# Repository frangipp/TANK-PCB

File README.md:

Dans le cadre d’un projet étudiant en binôme à l’ESEO Angers.

Développement d’un "TANK" : un petit robot à entraînement différentiel. Il sera commandé par Bluetooth via une application Android.
Pour l’utilisateur, l’objectif sera d’entrer en collision avec le TANK adverse. Chaque collision rapporte des points.

Détails techniques :

* Microcontrôleur STM32G431
* Module Bluetooth HC-05
* Négociation USB Power Delivery (STUSB4531)
* Chargeur et BMS pour batterie Li-ion (power management : BQ24800, équilibrage des cellules : BQ76905)
* Driver moteur LMD18200. Moteurs jusqu’à 55 V (théorique) et 3 A. On utilise ici des Maxon en 12 V.

À titre personnel, ce projet me permet surtout de tester la norme USB Power Delivery ainsi que la charge d’une batterie.

### Restrictions on Automated Processing and AI Usage

The author explicitly prohibits any text and data mining (TDM), scraping, indexing, or use of this project for training, evaluating, or operating artificial intelligence systems, unless prior written permission is obtained.

All rights are reserved in this regard, including under applicable EU directives on text and data mining.

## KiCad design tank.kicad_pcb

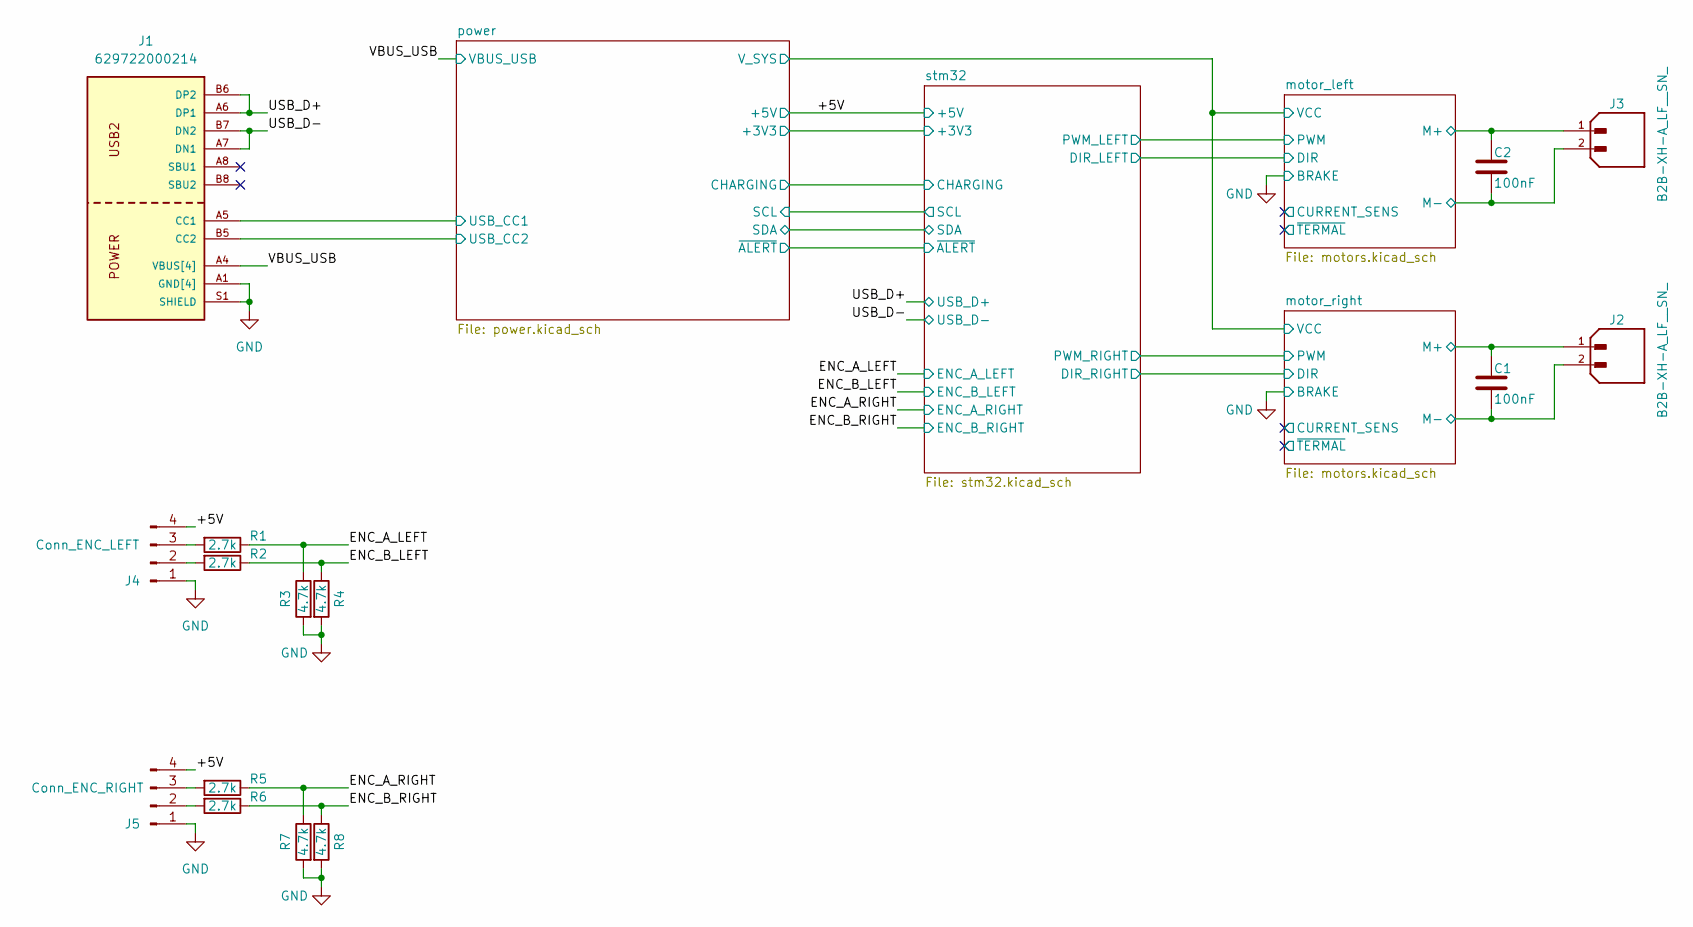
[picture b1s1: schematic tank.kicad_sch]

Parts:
C1, C2: 100nF; C_0603_1608Metric
J1: 629722000214
J2, J3: B2B-XH-A_LF__SN_; JST_B2B-XH-A_LF__SN_
J4: Conn_ENC_LEFT; PinHeader_1x04_P2.54mm_Vertical
J5: Conn_ENC_RIGHT; PinHeader_1x04_P2.54mm_Vertical
R1, R2, R5, R6: 2.7k; R_0603_1608Metric
R3, R4, R7, R8: 4.7k; R_0603_1608Metric

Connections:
/+5V: J4.4, J5.4; also elsewhere on the board
/ENC_A_LEFT: R1.1, R3.1; also elsewhere on the board
/ENC_A_RIGHT: R5.1, R7.1; also elsewhere on the board
/ENC_B_LEFT: R2.1, R4.1; also elsewhere on the board
/ENC_B_RIGHT: R6.1, R8.1; also elsewhere on the board
/USB_D+: J1.A6 (DP1), J1.B6 (DP2); also elsewhere on the board
/USB_D-: J1.A7 (DN1), J1.B7 (DN2); also elsewhere on the board
/VBUS_USB: J1.A4 (VBUS[4]), J1.A9 (VBUS[4]), J1.B4 (VBUS[4]), J1.B9 (VBUS[4]); also elsewhere on the board
/motor_left/M+: C2.1, J3.1; also elsewhere on the board
/motor_left/M-: C2.2, J3.2; also elsewhere on the board
/motor_right/M+: C1.1, J2.1; also elsewhere on the board
/motor_right/M-: C1.2, J2.2; also elsewhere on the board
/power/USB_CC1: J1.A5 (CC1); also elsewhere on the board
/power/USB_CC2: J1.B5 (CC2); also elsewhere on the board
GND: J1.A1 (GND[4]), J1.A12 (GND[4]), J1.B1 (GND[4]), J1.B12 (GND[4]), J1.S1 (SHIELD), J1.S2, J1.S3, J1.S4, J4.1, J5.1, R3.2, R4.2, R7.2, R8.2; also elsewhere on the board
unnamed: J4.2, R2.2
unnamed: J4.3, R1.2
unnamed: J5.2, R6.2
unnamed: J5.3, R5.2

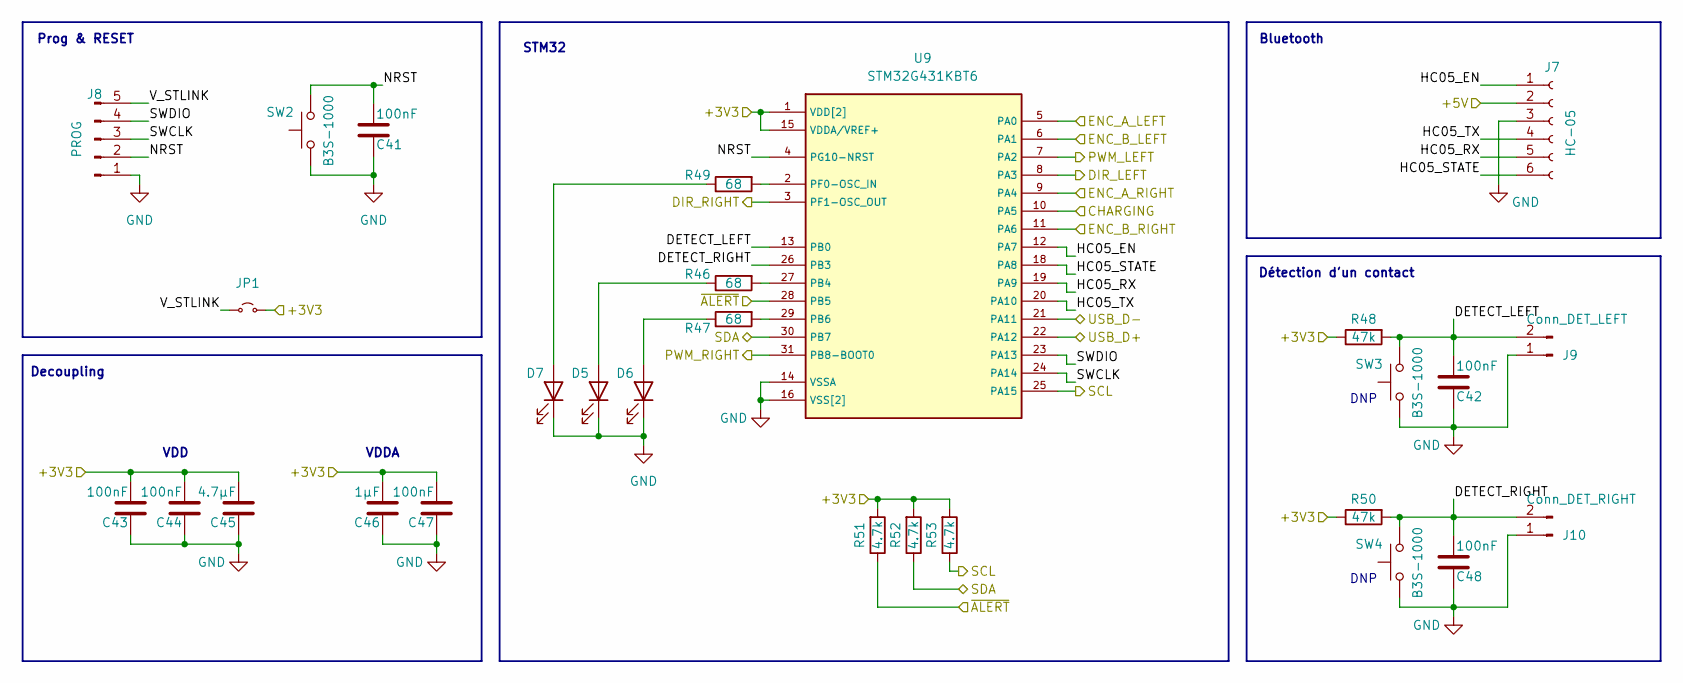
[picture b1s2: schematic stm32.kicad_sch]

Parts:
C41, C42, C43, C44, C47, C48: 100nF; C_0603_1608Metric
C45: 4.7µF; C_0805_2012Metric
C46: 1µF; C_0603_1608Metric
D5, D6, D7: LED; LED_0603_1608Metric
J7: HC-05; PinSocket_1x06_P2.54mm_Vertical
J8: PROG; PinHeader_1x05_P2.54mm_Vertical
J9: Conn_DET_LEFT; PinHeader_1x02_P2.54mm_Vertical
J10: Conn_DET_RIGHT; PinHeader_1x02_P2.54mm_Vertical
JP1: Jumper_2_Small_Open; PinHeader_1x02_P2.54mm_Vertical
R46, R47, R49: 68; R_0603_1608Metric
R48, R50: 47k; R_0603_1608Metric
R51, R52, R53: 4.7k; R_0603_1608Metric
SW2, SW3, SW4: B3S-1000; SW_SPST_B3S-1000
U9: STM32G431KBT6; QFP80P900X900X160-32N

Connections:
/+5V: J7.2; also elsewhere on the board
/ENC_A_LEFT: U9.5 (PA0); also elsewhere on the board
/ENC_A_RIGHT: U9.9 (PA4); also elsewhere on the board
/ENC_B_LEFT: U9.6 (PA1); also elsewhere on the board
/ENC_B_RIGHT: U9.11 (PA6); also elsewhere on the board
/USB_D+: U9.22 (PA12); also elsewhere on the board
/USB_D-: U9.21 (PA11); also elsewhere on the board
/motor_left/DIR: U9.8 (PA3); also elsewhere on the board
/motor_left/PWM: U9.7 (PA2); also elsewhere on the board
/motor_right/DIR: U9.3 (PF1-OSC_OUT); also elsewhere on the board
/motor_right/PWM: U9.31 (PB8-BOOT0); also elsewhere on the board
/power/CHARGING: U9.10 (PA5); also elsewhere on the board
/power/SCL: R53.1, U9.25 (PA15); also elsewhere on the board
/power/SDA: R52.1, U9.30 (PB7); also elsewhere on the board
/power/~ALERT: R51.1, U9.28 (PB5); also elsewhere on the board
/stm32/DETECT_LEFT: C42.2, J9.2, R48.2, SW3.2, U9.13 (PB0)
/stm32/DETECT_RIGHT: C48.2, J10.2, R50.2, SW4.2, U9.26 (PB3)
/stm32/HC05_EN: J7.1, U9.12 (PA7)
/stm32/HC05_RX: J7.5, U9.19 (PA9)
/stm32/HC05_STATE: J7.6, U9.18 (PA8)
/stm32/HC05_TX: J7.4, U9.20 (PA10)
/stm32/NRST: C41.2, J8.2, SW2.2, U9.4 (PG10-NRST)
/stm32/SWCLK: J8.3, U9.24 (PA14)
/stm32/SWDIO: J8.4, U9.23 (PA13)
/stm32/V_STLINK: J8.5, JP1.1 (A)
GND: C41.1, C42.1, C43.1, C44.1, C45.1, C46.1, C47.1, C48.1, D5.1 (K), D6.1 (K), D7.1 (K), J7.3, J8.1, J9.1, J10.1, SW2.1, SW3.1, SW4.1, U9.14 (VSSA), U9.16 (VSS[2]), U9.32 (VSS); also elsewhere on the board
unnamed: D5.2 (A), R46.1
unnamed: D6.2 (A), R47.1
unnamed: D7.2 (A), R49.1
unnamed: R46.2, U9.27 (PB4)
unnamed: R47.2, U9.29 (PB6)
unnamed: R49.2, U9.2 (PF0-OSC_IN)
VDD: C43.2, C44.2, C45.2, C46.2, C47.2, JP1.2 (B), R48.1, R50.1, R51.2, R52.2, R53.2, U9.1 (VDD[2]), U9.15 (VDDA/VREF+), U9.17 (VDD); also elsewhere on the board

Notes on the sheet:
VDDA
Détection d'un contact
Bluetooth
DNP
VDD
Decoupling
Prog & RESET
STM32

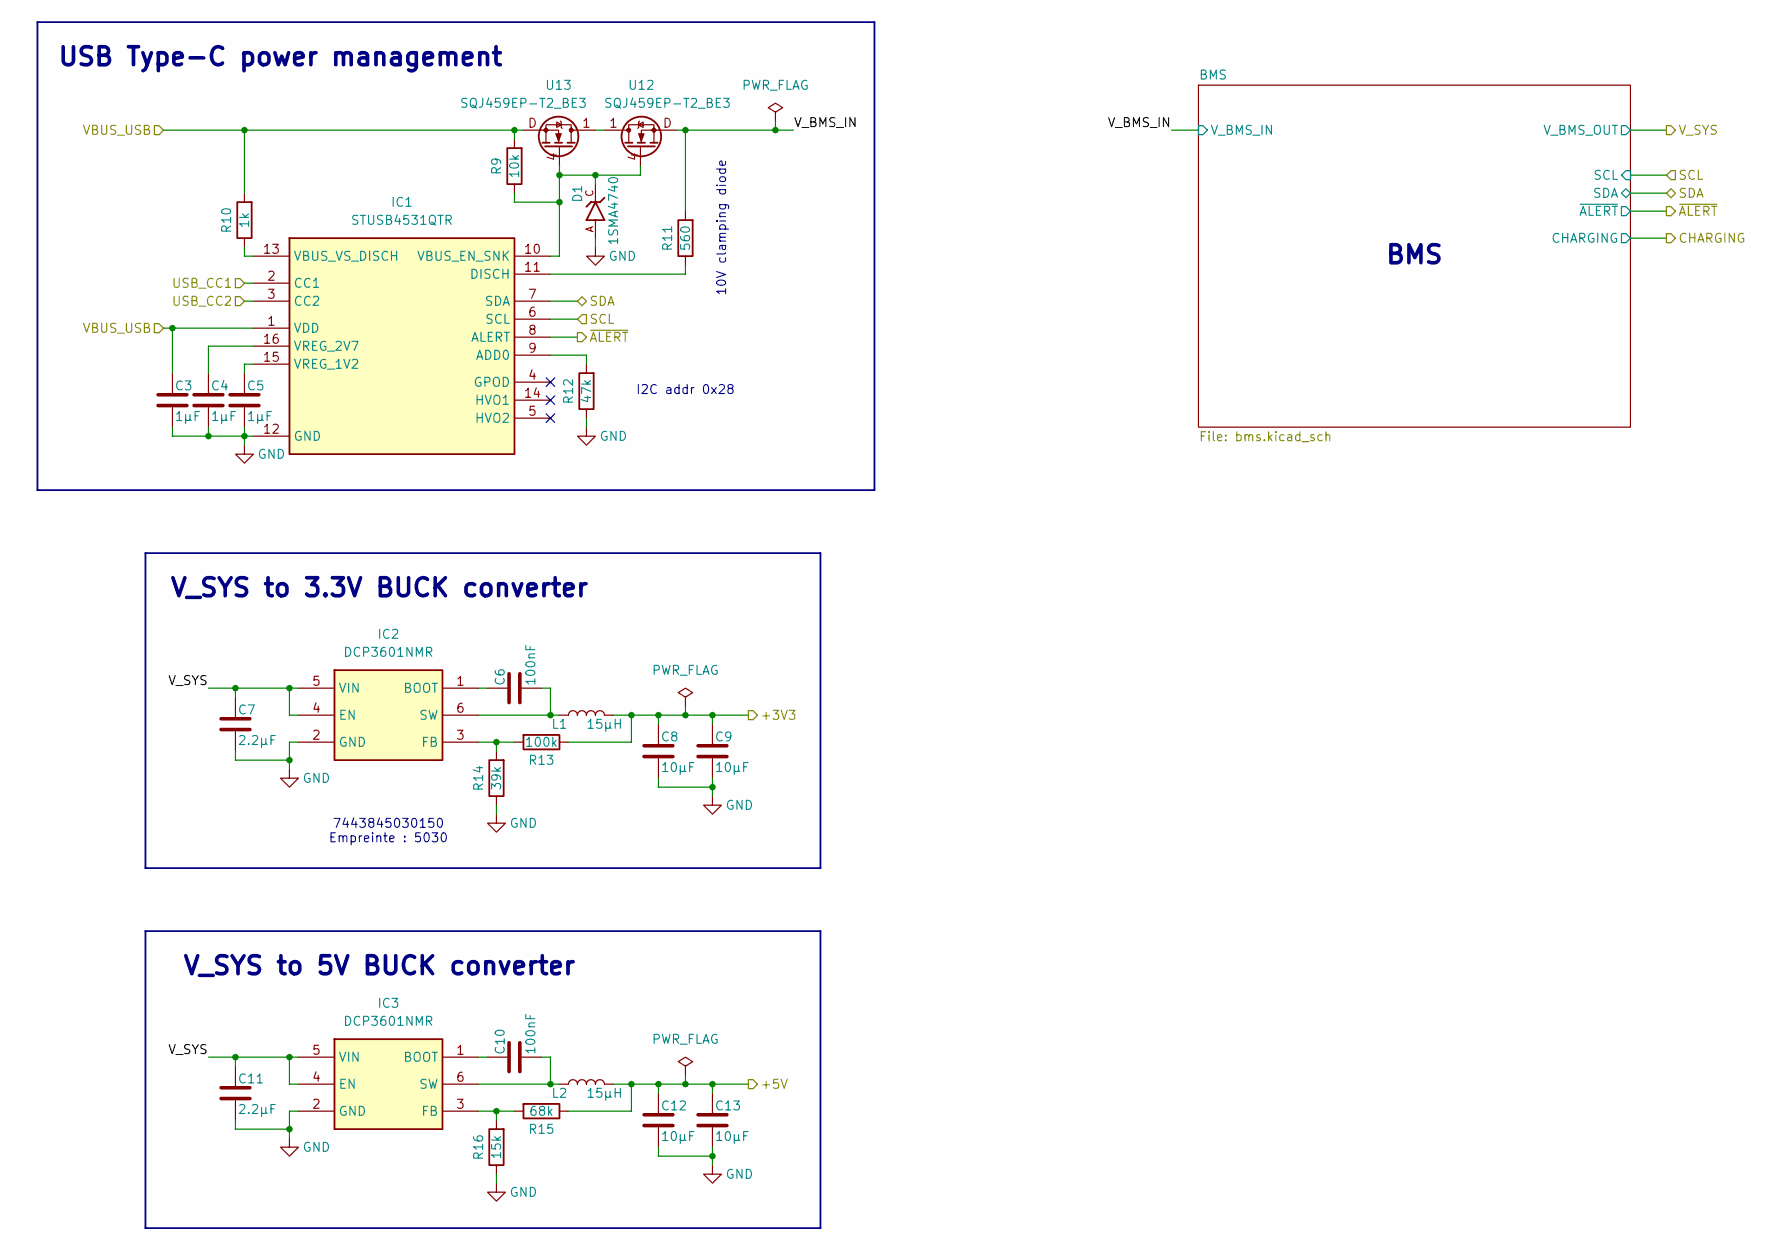
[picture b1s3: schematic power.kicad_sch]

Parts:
C3, C4, C5: 1µF; C_0603_1608Metric
C6, C10: 100nF; C_0603_1608Metric
C7, C11: 2.2µF; C_0603_1608Metric
C8, C9, C12, C13: 10µF; C_0805_2012Metric
D1: 1SMA4740; DIOM4325X250N
IC1: STUSB4531QTR; QFN50P300X300X65-16N-D
IC2, IC3: DCP3601NMR; SOT95P280X125-6N; Mouser Part Number 511-DCP3601NMR
L1, L2: 15µH; L_Wuerth_MAPI-5030
R9: 10k; R_0603_1608Metric
R10: 1k; R_0603_1608Metric
R11: 560; R_0603_1608Metric
R12: 47k; R_0603_1608Metric
R13: 100k; R_0603_1608Metric
R14: 39k; R_0603_1608Metric
R15: 68k; R_0603_1608Metric
R16: 15k; R_0603_1608Metric
U12, U13: SQJ459EP-T2_BE3; SIJA54DPT1GE3

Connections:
/+5V: C12.1, C13.1, L2.2, R15.1; also elsewhere on the board
/VBUS_USB: C3.1, IC1.1 (VDD), R9.2, R10.2, U13.D; also elsewhere on the board
/power/SCL: IC1.6 (SCL); also elsewhere on the board
/power/SDA: IC1.7 (SDA); also elsewhere on the board
/power/USB_CC1: IC1.2 (CC1); also elsewhere on the board
/power/USB_CC2: IC1.3 (CC2); also elsewhere on the board
/power/V_BMS_IN: R11.2, U12.D; also elsewhere on the board
/power/V_SYS: C7.1, C11.1, IC2.4 (EN), IC2.5 (VIN), IC3.4 (EN), IC3.5 (VIN); also elsewhere on the board
/power/~ALERT: IC1.8 (ALERT); also elsewhere on the board
GND: C3.2, C4.2, C5.2, C7.2, C8.2, C9.2, C11.2, C12.2, C13.2, D1.A, IC1.12 (GND), IC2.2 (GND), IC3.2 (GND), R12.1, R14.1, R16.1; also elsewhere on the board
unnamed: IC1.9 (ADD0), R12.2
unnamed: IC1.11 (DISCH), R11.1
unnamed: D1.C, IC1.10 (VBUS_EN_SNK), R9.1, U12.4, U13.4
unnamed: IC1.13 (VBUS_VS_DISCH), R10.1
unnamed: C5.1, IC1.15 (VREG_1V2)
unnamed: C4.1, IC1.16 (VREG_2V7)
unnamed: C6.1, IC2.1 (BOOT)
unnamed: IC2.3 (FB), R13.2, R14.2
unnamed: C6.2, IC2.6 (SW), L1.1
unnamed: C10.1, IC3.1 (BOOT)
unnamed: IC3.3 (FB), R15.2, R16.2
unnamed: C10.2, IC3.6 (SW), L2.1
unnamed: U12.1, U12.2, U12.3, U13.1, U13.2, U13.3
VDD: C8.1, C9.1, L1.2, R13.1; also elsewhere on the board

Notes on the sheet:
USB Type-C power management
BMS
V_SYS to 3.3V BUCK converter
I2C addr 0x28
V_SYS to 5V BUCK converter
10V clamping diode
7443845030150 Empreinte : 5030

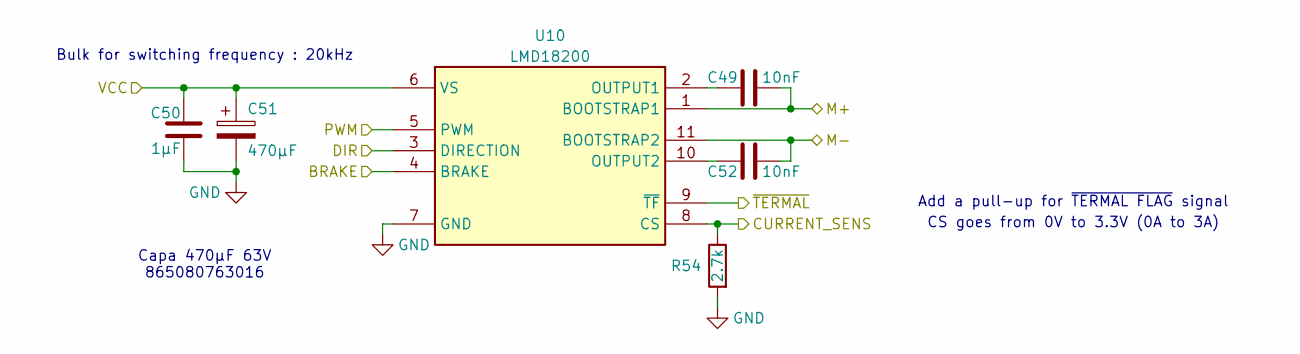
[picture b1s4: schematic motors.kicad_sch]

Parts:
C49, C52: 10nF; C_0603_1608Metric
C50: 1µF; C_0603_1608Metric
C51: 470µF; CP_Elec_16x17.5
R54: 2.7k; R_0603_1608Metric
U10: LMD18200

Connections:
/motor_right/CURRENT_SENS: R54.1, U10.8 (CS)
/motor_right/DIR: U10.3 (DIRECTION); also elsewhere on the board
/motor_right/M+: C49.2, U10.1 (BOOTSTRAP1); also elsewhere on the board
/motor_right/M-: C52.2, U10.11 (BOOTSTRAP2); also elsewhere on the board
/motor_right/PWM: U10.5 (PWM); also elsewhere on the board
/motor_right/~TERMAL: U10.9 (~TF)
/power/V_SYS: C50.1, C51.1, U10.6 (VS); also elsewhere on the board
GND: C50.2, C51.2, R54.2, U10.4 (BRAKE), U10.7 (GND); also elsewhere on the board
unnamed: C49.1, U10.2 (OUTPUT1)
unnamed: C52.1, U10.10 (OUTPUT2)

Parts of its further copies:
C53, C56: 10nF; C_0603_1608Metric
C54: 1µF; C_0603_1608Metric
C55: 470µF; CP_Elec_16x17.5
R55: 2.7k; R_0603_1608Metric
U11: LMD18200

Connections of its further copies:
/motor_left/CURRENT_SENS: R55.1, U11.8 (CS)
/motor_left/DIR: U11.3 (DIRECTION); also elsewhere on the board
/motor_left/M+: C53.2, U11.1 (BOOTSTRAP1); also elsewhere on the board
/motor_left/M-: C56.2, U11.11 (BOOTSTRAP2); also elsewhere on the board
/motor_left/PWM: U11.5 (PWM); also elsewhere on the board
/motor_left/~TERMAL: U11.9 (~TF)
/power/V_SYS: C54.1, C55.1, U11.6 (VS); also elsewhere on the board
GND: C54.2, C55.2, R55.2, U11.4 (BRAKE), U11.7 (GND); also elsewhere on the board
unnamed: C53.1, U11.2 (OUTPUT1)
unnamed: C56.1, U11.10 (OUTPUT2)

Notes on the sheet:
Add a pull-up for ~{TERMAL FLAG} signal
Bulk for switching frequency : 20kHz
Capa 470µF 63V 865080763016
CS goes from 0V to 3.3V (0A to 3A)

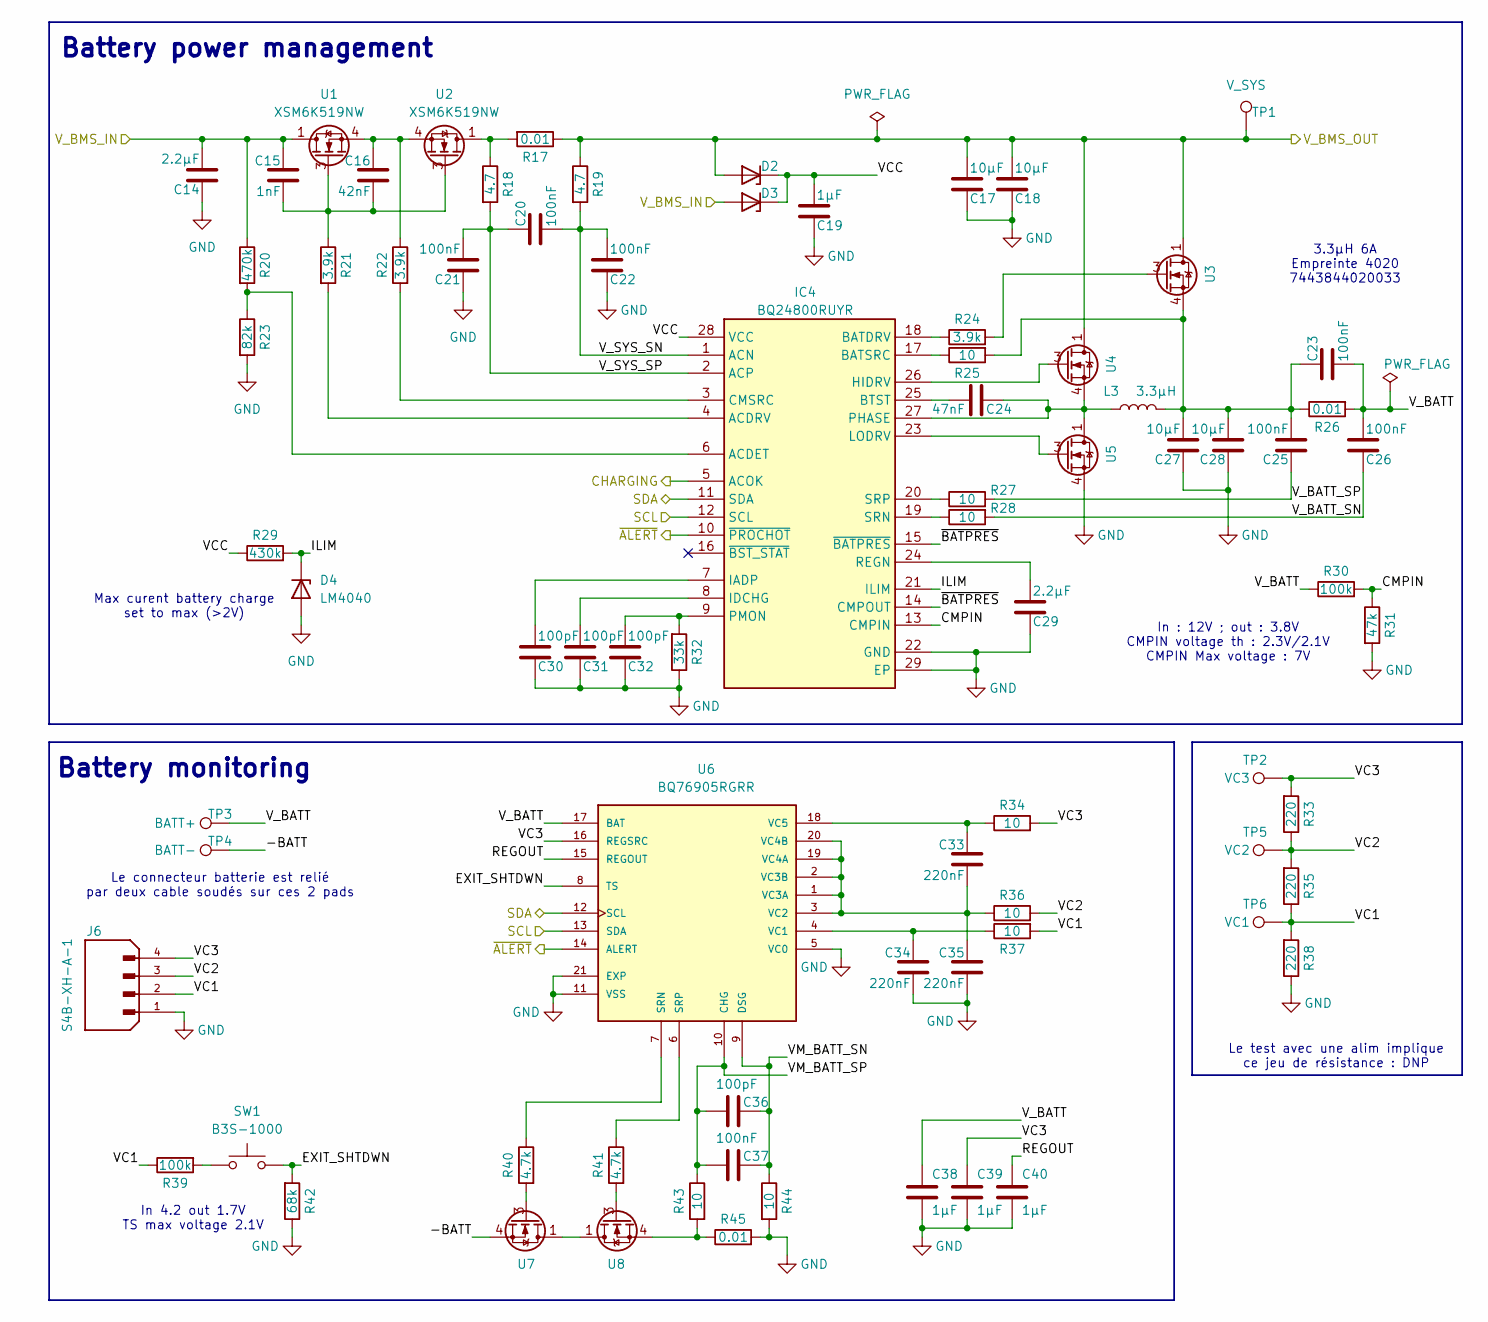
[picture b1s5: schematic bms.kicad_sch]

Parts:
C14, C29: 2.2µF; C_0603_1608Metric
C15: 1nF; C_0603_1608Metric
C16: 42nF; C_0603_1608Metric
C17, C18, C27, C28: 10µF; C_0805_2012Metric
C19, C38, C39, C40: 1µF; C_0603_1608Metric
C20, C21, C22, C23, C25, C26, C37: 100nF; C_0603_1608Metric
C24: 47nF; C_0603_1608Metric
C30, C31, C32, C36: 100pF; C_0603_1608Metric
C33, C34, C35: 220nF; C_0603_1608Metric
D2, D3: DIO_MM3Z3V0T1G
D4: LM4040; SOT95P237X112-3N
IC4: BQ24800RUYR; QFN40P400X400X80-29N-D; Manufacturer_Part_Number BQ24810RUYR
J6: S4B-XH-A-1; JST_S4B-XH-A-1
L3: 3.3µH; L_Wuerth_MAPI-4020
R17, R26, R45: 0.01; RESC6331X88N
R18, R19: 4.7; R_0603_1608Metric
R20: 470k; R_0603_1608Metric
R21, R22, R24: 3.9k; R_0603_1608Metric
R23: 82k; R_0603_1608Metric
R25, R27, R28, R34, R36, R37, R43, R44: 10; R_0603_1608Metric
R29: 430k; R_0603_1608Metric
R30, R39: 100k; R_0603_1608Metric
R31: 47k; R_0603_1608Metric
R32: 33k; R_0603_1608Metric
R33, R35, R38: 220; R_0805_2012Metric
R40, R41: 4.7k; R_0603_1608Metric
R42: 68k; R_0603_1608Metric
SW1: B3S-1000; SW_SPST_B3S-1000
TP1: V_SYS; TestPoint_Pad_D1.0mm
TP2: VC3; TestPoint_Pad_D1.0mm
TP3: BATT+; TestPoint_THTPad_D4.0mm_Drill2.0mm
TP4: BATT-; TestPoint_THTPad_D4.0mm_Drill2.0mm
TP5: VC2; TestPoint_Pad_D1.0mm
TP6: VC1; TestPoint_Pad_D1.0mm
U1, U2, U3, U4, U5, U7, U8: XSM6K519NW; DFN2020MD-6_SOT1220_NEX
U6: BQ76905RGRR; IC_BQ76905RGRR

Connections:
/power/BMS/-BATT: TP4.1 (1_1), U7.4, U7.8
/power/BMS/CMPIN: IC4.13 (CMPIN), R30.2, R31.1
/power/BMS/EXIT_SHTDWN: R42.2, SW1.2, U6.8 (TS)
/power/BMS/ILIM: D4.1 (K), IC4.21 (ILIM), R29.2
/power/BMS/REGOUT: C40.2, U6.15 (REGOUT)
/power/BMS/VC1: J6.2, R35.1, R37.2, R38.2, R39.1, TP6.1 (1_1)
/power/BMS/VC2: J6.3, R33.1, R35.2, R36.2, TP5.1 (1_1)
/power/BMS/VC3: C39.2, J6.4, R33.2, R34.2, TP2.1 (1_1), U6.16 (REGSRC)
/power/BMS/VCC: C19.2, D2.1 (K), D3.1 (K), IC4.28 (VCC), R29.1
/power/BMS/VM_BATT_SN: C36.1, C37.1, R44.1, U6.9 (DSG)
/power/BMS/VM_BATT_SP: C36.2, C37.2, R43.1, U6.10 (CHG)
/power/BMS/V_BATT: C23.2, C26.2, C38.2, R26.2, R30.1, TP3.1 (1_1), U6.17 (BAT)
/power/BMS/V_BATT_SN: C26.1, R28.2
/power/BMS/V_BATT_SP: C25.1, R27.2
/power/BMS/V_SYS_SN: C20.2, C22.2, IC4.1 (ACN), R19.2
/power/BMS/V_SYS_SP: C20.1, C21.2, IC4.2 (ACP), R18.2
/power/BMS/~BATPRES: IC4.14 (CMPOUT), IC4.15 (~BATPRES)
/power/CHARGING: IC4.5 (ACOK); also elsewhere on the board
/power/SCL: IC4.12 (SCL), U6.13 (SDA); also elsewhere on the board
/power/SDA: IC4.11 (SDA), U6.12 (SCL); also elsewhere on the board
/power/V_BMS_IN: C14.2, C15.1, D3.2 (A), R20.1, U1.1, U1.2, U1.5, U1.6, U1.7; also elsewhere on the board
/power/V_SYS: C17.2, C18.2, D2.2 (A), R17.1, R19.1, TP1.1 (1_1), U3.1, U3.2, U3.5, U3.6, U3.7, U4.1, U4.2, U4.5, U4.6, U4.7; also elsewhere on the board
/power/~ALERT: IC4.10 (~PROCHOT), U6.14 (ALERT); also elsewhere on the board
GND: C14.1, C17.1, C18.1, C19.1, C21.1, C22.1, C27.1, C28.1, C29.1, C30.1, C31.1, C32.1, C34.2, C35.2, C38.1, C39.1, C40.1, D4.2 (A), D4.3 (*), IC4.22 (GND), IC4.29 (EP), J6.1, R23.2, R31.2, R32.1, R38.1, R42.1, R44.2, R45.2, U5.4, U5.8, U6.5 (VC0), U6.11 (VSS), U6.21 (EXP); also elsewhere on the board
unnamed: C15.2, C16.2, R21.1, U1.3, U2.3
unnamed: C16.1, R22.1, U1.4, U1.8, U2.4, U2.8
unnamed: C23.1, C25.2, C27.2, C28.2, L3.2, R25.2, R26.1, U3.4, U3.8
unnamed: IC4.6 (ACDET), R20.2, R23.1
unnamed: IC4.4 (ACDRV), R21.2
unnamed: IC4.18 (BATDRV), R24.1
unnamed: IC4.17 (BATSRC), R25.1
unnamed: C24.2, IC4.25 (BTST)
unnamed: IC4.3 (CMSRC), R22.2
unnamed: IC4.26 (HIDRV), U4.3
unnamed: C30.2, IC4.7 (IADP)
unnamed: C31.2, IC4.8 (IDCHG)
unnamed: IC4.23 (LODRV), U5.3
unnamed: C24.1, IC4.27 (PHASE), L3.1, U4.4, U4.8, U5.1, U5.2, U5.5, U5.6, U5.7
unnamed: C32.2, IC4.9 (PMON), R32.2
unnamed: C29.2, IC4.24 (REGN)
unnamed: IC4.19 (SRN), R28.1
unnamed: IC4.20 (SRP), R27.1
unnamed: R17.2, R18.1, U2.1, U2.2, U2.5, U2.6, U2.7
unnamed: R24.2, U3.3
unnamed: R39.2, SW1.1
unnamed: R40.2, U7.3
unnamed: R41.2, U8.3
unnamed: R43.2, R45.1, U8.4, U8.8
unnamed: R40.1, U6.7 (SRN)
unnamed: R41.1, U6.6 (SRP)
unnamed: C34.1, R37.1, U6.4 (VC1)
unnamed: C33.2, C35.1, R36.1, U6.1 (VC3A), U6.2 (VC3B), U6.3 (VC2), U6.19 (VC4A), U6.20 (VC4B)
unnamed: C33.1, R34.1, U6.18 (VC5)
unnamed: U7.1, U7.2, U7.5, U7.6, U7.7, U8.1, U8.2, U8.5, U8.6, U8.7

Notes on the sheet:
Le connecteur batterie est relié par deux cable soudés sur ces 2 pads
In : 12V ; out : 3.8V CMPIN voltage th : 2.3V/2.1V CMPIN Max voltage : 7V
Battery power management
Max curent battery charge set to max (>2V)
3.3µH 6A Empreinte 4020 7443844020033
In 4.2 out 1.7V TS max voltage 2.1V
Battery monitoring
Le test avec une alim implique ce jeu de résistance : DNP

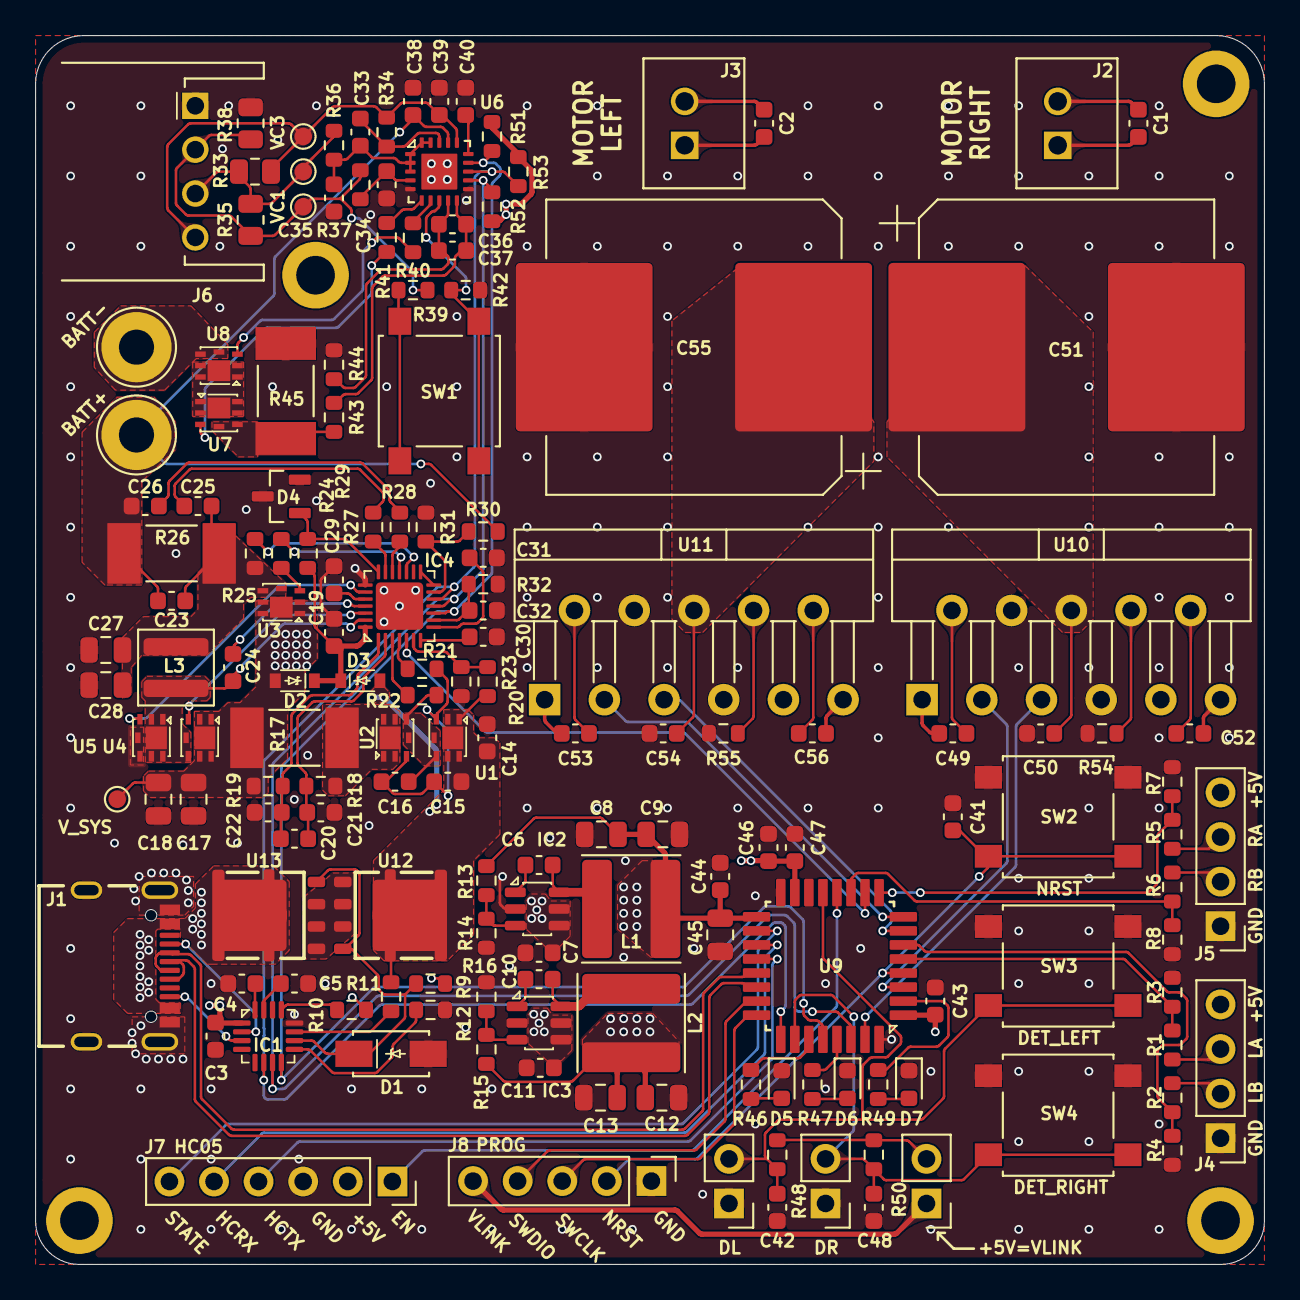
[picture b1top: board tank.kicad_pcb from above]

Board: 4 copper layers, 70.0 x 70.0 mm, 159 parts (0 on the bottom side), 112 nets.

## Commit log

2026-03-07 Clean repository and apply gitignore
2026-03-11 Ajouts de 3 feuilles de travail (motors/stm32/power). Ajout de la négociation USB-PD. Ajout d'un régulateur BUCK 3,3V.
2026-03-12 Ajout du BMS
2026-03-14 Update BMS
2026-03-14 Ajout des deux moteurs
2026-03-16 Version 0. Schémas finalisés. Mise à jour des résistances en série E12. Réduction de la BOM.
2026-03-25 Minor Schematics update
2026-03-27 Add project overview and technical specifications
    Added project description and technical details for TANK robot.
2026-03-31 Modification mineur du schéma, ajout du PCB V1
2026-04-01 Léger remapping du stm32.
2026-04-03 Modifications mineurs du schéma. Passage sous Kicad 10 ok. Finalisations PCB (teardrops, arrondis)
2026-04-03 Ajout d'une license
2026-04-03 Génération pdf du schéma
